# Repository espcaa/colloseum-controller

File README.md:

# The Colloseum-controller

What's colloseum? Simply the greatest smash-like tournament game ever, happening @highway (https://highway.hackclub.com), a hardware hackathon at github hq

## Wow look at it!!!!

## What is that, how does it works???

Based of an CH552G it can act as a usb keyboard so that your pc recognize it as a keyboard without any specific driver!
It uses quite a few techniques to bring down cost, everything is tht, the usb port is just a trace on the pcb, making it around 2-4$/board (hopefully)

## BOM

(prices for 1 unit, at 50 costs will go -50% thanks to lcsc)

| Name     | Units | Price       | LCSC Number
|----------|-----|------------|-------|
| CH552G    | 1  | 0.5575      | C111292 |
| 3mm led (any color) | 4 | 0.0228 | C2895458 |
| Resistors | 5 | 0.5 | NA |
| Button | 2 | 0.0466 | C22459507 |
| Joystick | 1 | 0.40 | C37323739 |
| PCB | 1 | 4.4 | NA |
| M3 Nut | 4 | 0.01 | C133377 |
| M3 Screw | 4 | .. | NA |

You also need some pla/petg/whatever to 3d print the case
The pcb can seem expensive but that's just the ENIG setup fee, we're at less than a dollar per pcb when ordering 50

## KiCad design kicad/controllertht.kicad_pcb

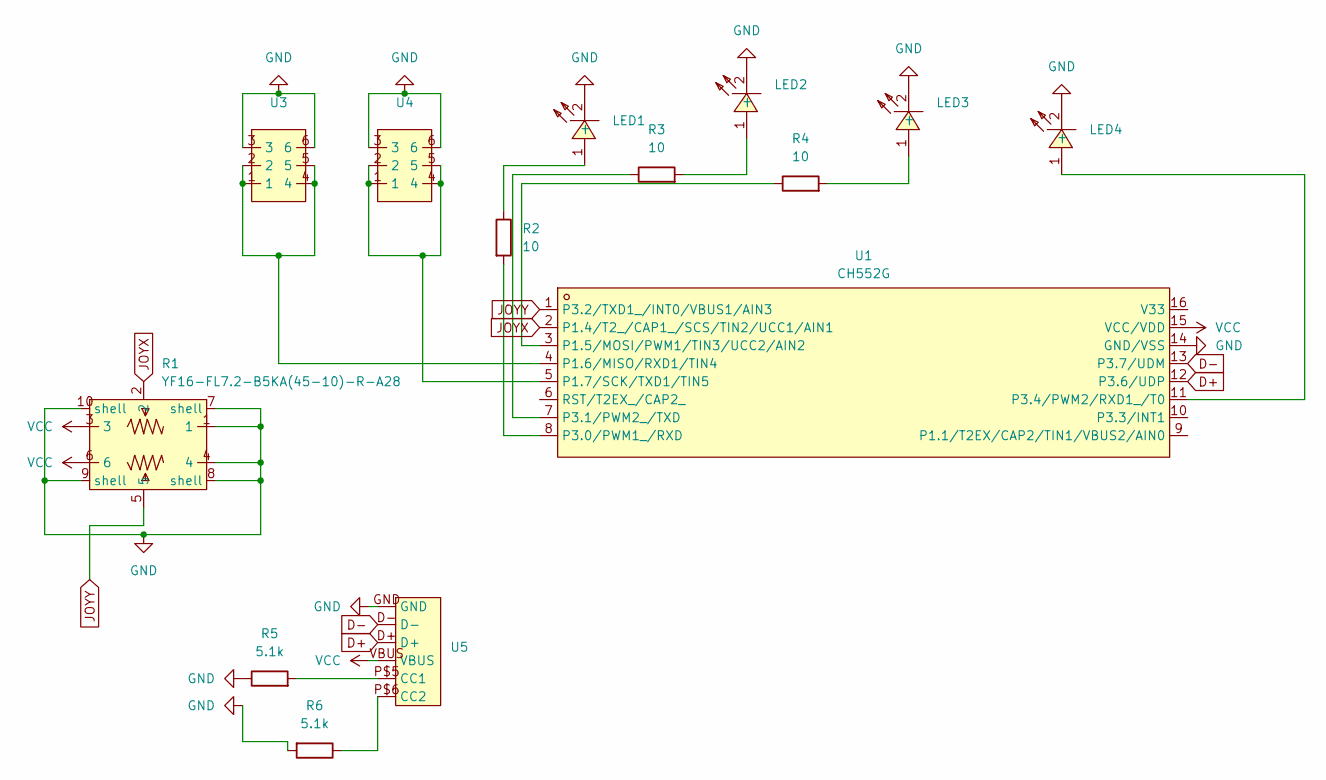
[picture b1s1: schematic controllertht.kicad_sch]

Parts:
LED1, LED2, LED3, LED4: 204-10SUBC/S400-A4; LED-TH_BD4.0-P2.54-FD; LCSC Part C86881
R1: YF16-FL7.2-B5KA(45-10)-R-A28; JOYTICK-TH_YF16-DFL7.2-B5KO-45-10-B5KO-55--RG-A22; LCSC Part C37323739
R2, R3, R4: 10; R_Axial_DIN0207_L6.3mm_D2.5mm_P7.62mm_Horizontal
R5, R6: 5.1k; R_Axial_DIN0207_L6.3mm_D2.5mm_P7.62mm_Horizontal
U1: CH552G; SOP-16_L10.0-W3.9-P1.27-LS6.0-BL; LCSC Part C111292
U3, U4: DIP6-DPDT
U5: USB_TYPE_C_W_2.0_5

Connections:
D+: U1.12 (P3.6/UDP), U5.D+
D-: U1.13 (P3.7/UDM), U5.D-
GND: LED1.2 (-), LED2.2 (-), LED3.2 (-), LED4.2 (-), R1.1, R1.4, R1.7 (shell), R1.8 (shell), R1.9 (shell), R1.10 (shell), R5.1, R6.2, U1.14 (GND/VSS), U3.3, U3.6, U4.3, U4.6, U5.GND
JOYX: R1.2, U1.2 (P1.4/T2_/CAP1_/SCS/TIN2/UCC1/AIN1)
JOYY: R1.5, U1.1 (P3.2/TXD1_/INT0/VBUS1/AIN3)
unnamed: LED1.1 (+), R2.1
unnamed: LED2.1 (+), R3.2
unnamed: LED3.1 (+), R4.2
unnamed: LED4.1 (+), U1.11 (P3.4/PWM2/RXD1_/T0)
unnamed: R4.1, U1.3 (P1.5/MOSI/PWM1/TIN3/UCC2/AIN2)
unnamed: U1.4 (P1.6/MISO/RXD1/TIN4), U3.1, U3.2, U3.4, U3.5
unnamed: U1.5 (P1.7/SCK/TXD1/TIN5), U4.1, U4.2, U4.4, U4.5
unnamed: R2.2, U1.8 (P3.0/PWM1_/RXD)
unnamed: R3.1, U1.7 (P3.1/PWM2_/TXD)
unnamed: R5.2, U5.P$5 (CC1)
unnamed: R6.1, U5.P$6 (CC2)
VCC: R1.3, R1.6, U1.15 (VCC/VDD), U5.VBUS

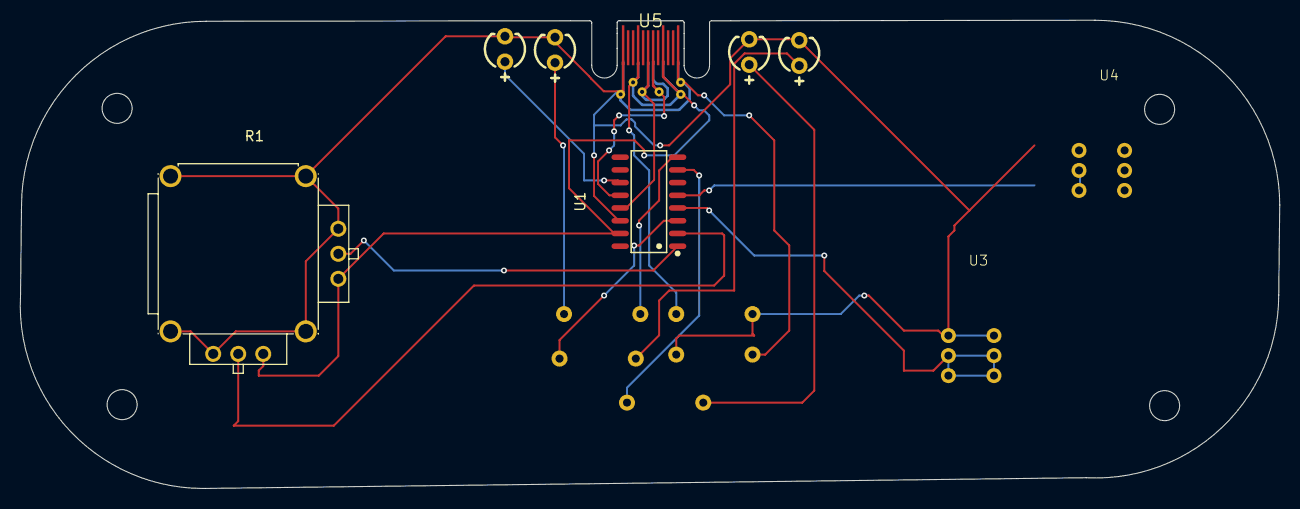
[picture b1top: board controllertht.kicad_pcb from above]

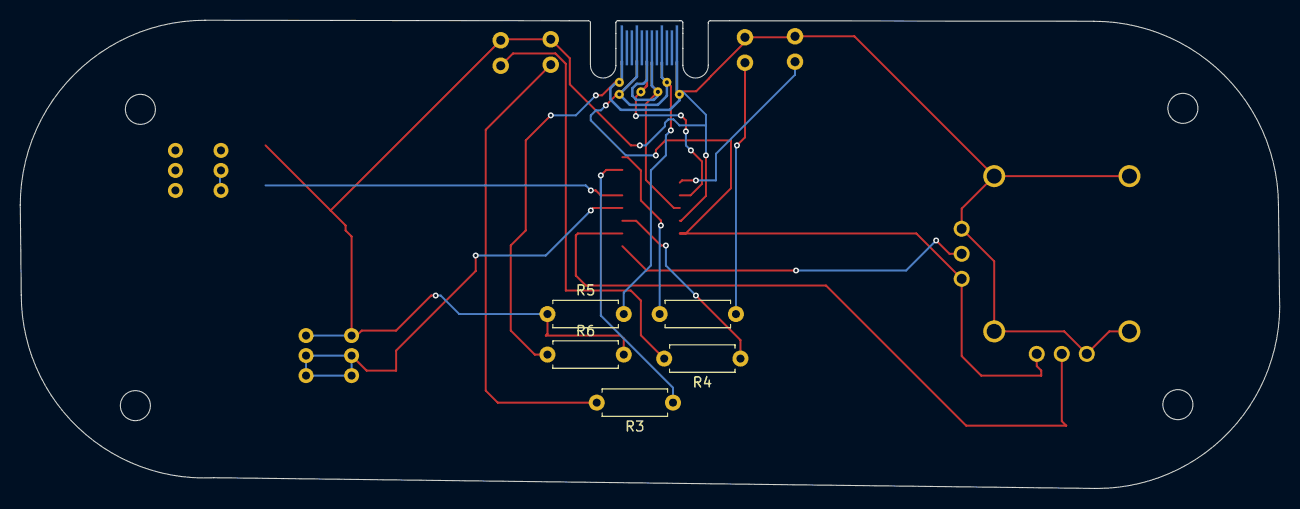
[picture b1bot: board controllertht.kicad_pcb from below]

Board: 2 copper layers, 125.8 x 46.8 mm, 14 parts (5 on the bottom side), 17 nets.

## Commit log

2025-06-22 added journal
2025-06-22 added kicad+onshape files
2025-06-22 added hours
2025-06-22 added bom
2025-06-22 fixed the button
2025-06-22 added gitignore
2025-06-22 idk if i removed all of them sob
2025-06-22 changed the format
2025-06-22 added m3 thingies
2025-06-24 tried to add more things
